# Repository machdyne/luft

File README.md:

# Luft Air Sensor Controller

Luft is an experimental open-source air sensor controller with sockets for up to four MQ gas sensor modules. In addition to MQ modules, you can also connect a SEN55 module (particulate matter, Volatile Organic Compounds, Nitrogen Oxides, humidity, and temperature) and a I2C oxygen sensor, CO₂ sensor, or other I2C sensors.

Luft enables remote monitoring of gasses, air quality and other environmental factors.

The alarm can be triggered by either the MCU or the MQ modules based on their potentiometer setting. The alarm is only activated when JP1 is shunted with a jumper or key switch.

This repo contains schematics, PCB layouts, a DIN-mountable 3D-printable case, and documentation.

Find more information on the [Luft product page](https://machdyne.com/product/luft-air-sensor-controller/).

## Configuration (Tasmota)

### Template

```
{"NAME":"LUFT-ESP32C3","GPIO":[8546,8547,1,8545,8544,1,3872,416,1,1,480,0,0,0,0,0,0,0,1,1,608,640],"FLAG":0,"BASE":1}
```

### Pinout

| GPIO | Function | Description |
| ---- | -------- | ----------- |
| GPIO0 | ADC MQ 3 | MQ3 analog |
| GPIO1 | ADC MQ 4 | MQ4 analog |
| GPIO3 | ADC MQ 2 | MQ2 analog |
| GPIO4 | ADC MQ 1 | MQ1 analog |
| GPIO6 | OUTPUT LOW | MQ power enable |
| GPIO7 | PWM 1 | Fan power control |
| GPIO10 | BUZZER | Buzzer power control |
| GPIO20 | I2C SCL | I2C clock |
| GPIO21 | I2C SDA | I2C data |

### Example Rules

```
# Send MQTT data every 60 seconds
TelePeriod 60

# Socket 1: MQ-135 (GPIO4)
AdcGpio4 135.00, 605.18, -3.937, 15.0

# Socket 2: MQ-2 (GPIO3)
AdcGpio3 2.00, 574.25, -2.22, 15.0

# Socket 3: MQ-6 (GPIO0)
AdcGpio0 6.00, 574.25, -2.22, 15.0

# Socket 4: MQ-9 (GPIO1)
AdcGpio1 9.00, 574.25, -2.22, 15.0
```

### Notes

If you have issues detecting the SEN55 module: https://github.com/arendst/Tasmota/discussions/19027

## Safety

This is an experimental design, use at your own risk. The heating elements in MQ modules can potentially ignite gasses. Luft is intended to be used with the 3D-printable case and an exhaust fan.

## License

The contents of this repo are released under the [Lone Dynamics Open License](LICENSE.md).

Note: You can use these designs for commercial purposes but we ask that instead of producing exact clones, that you either replace our trademarks and logos with your own or add your own next to ours.

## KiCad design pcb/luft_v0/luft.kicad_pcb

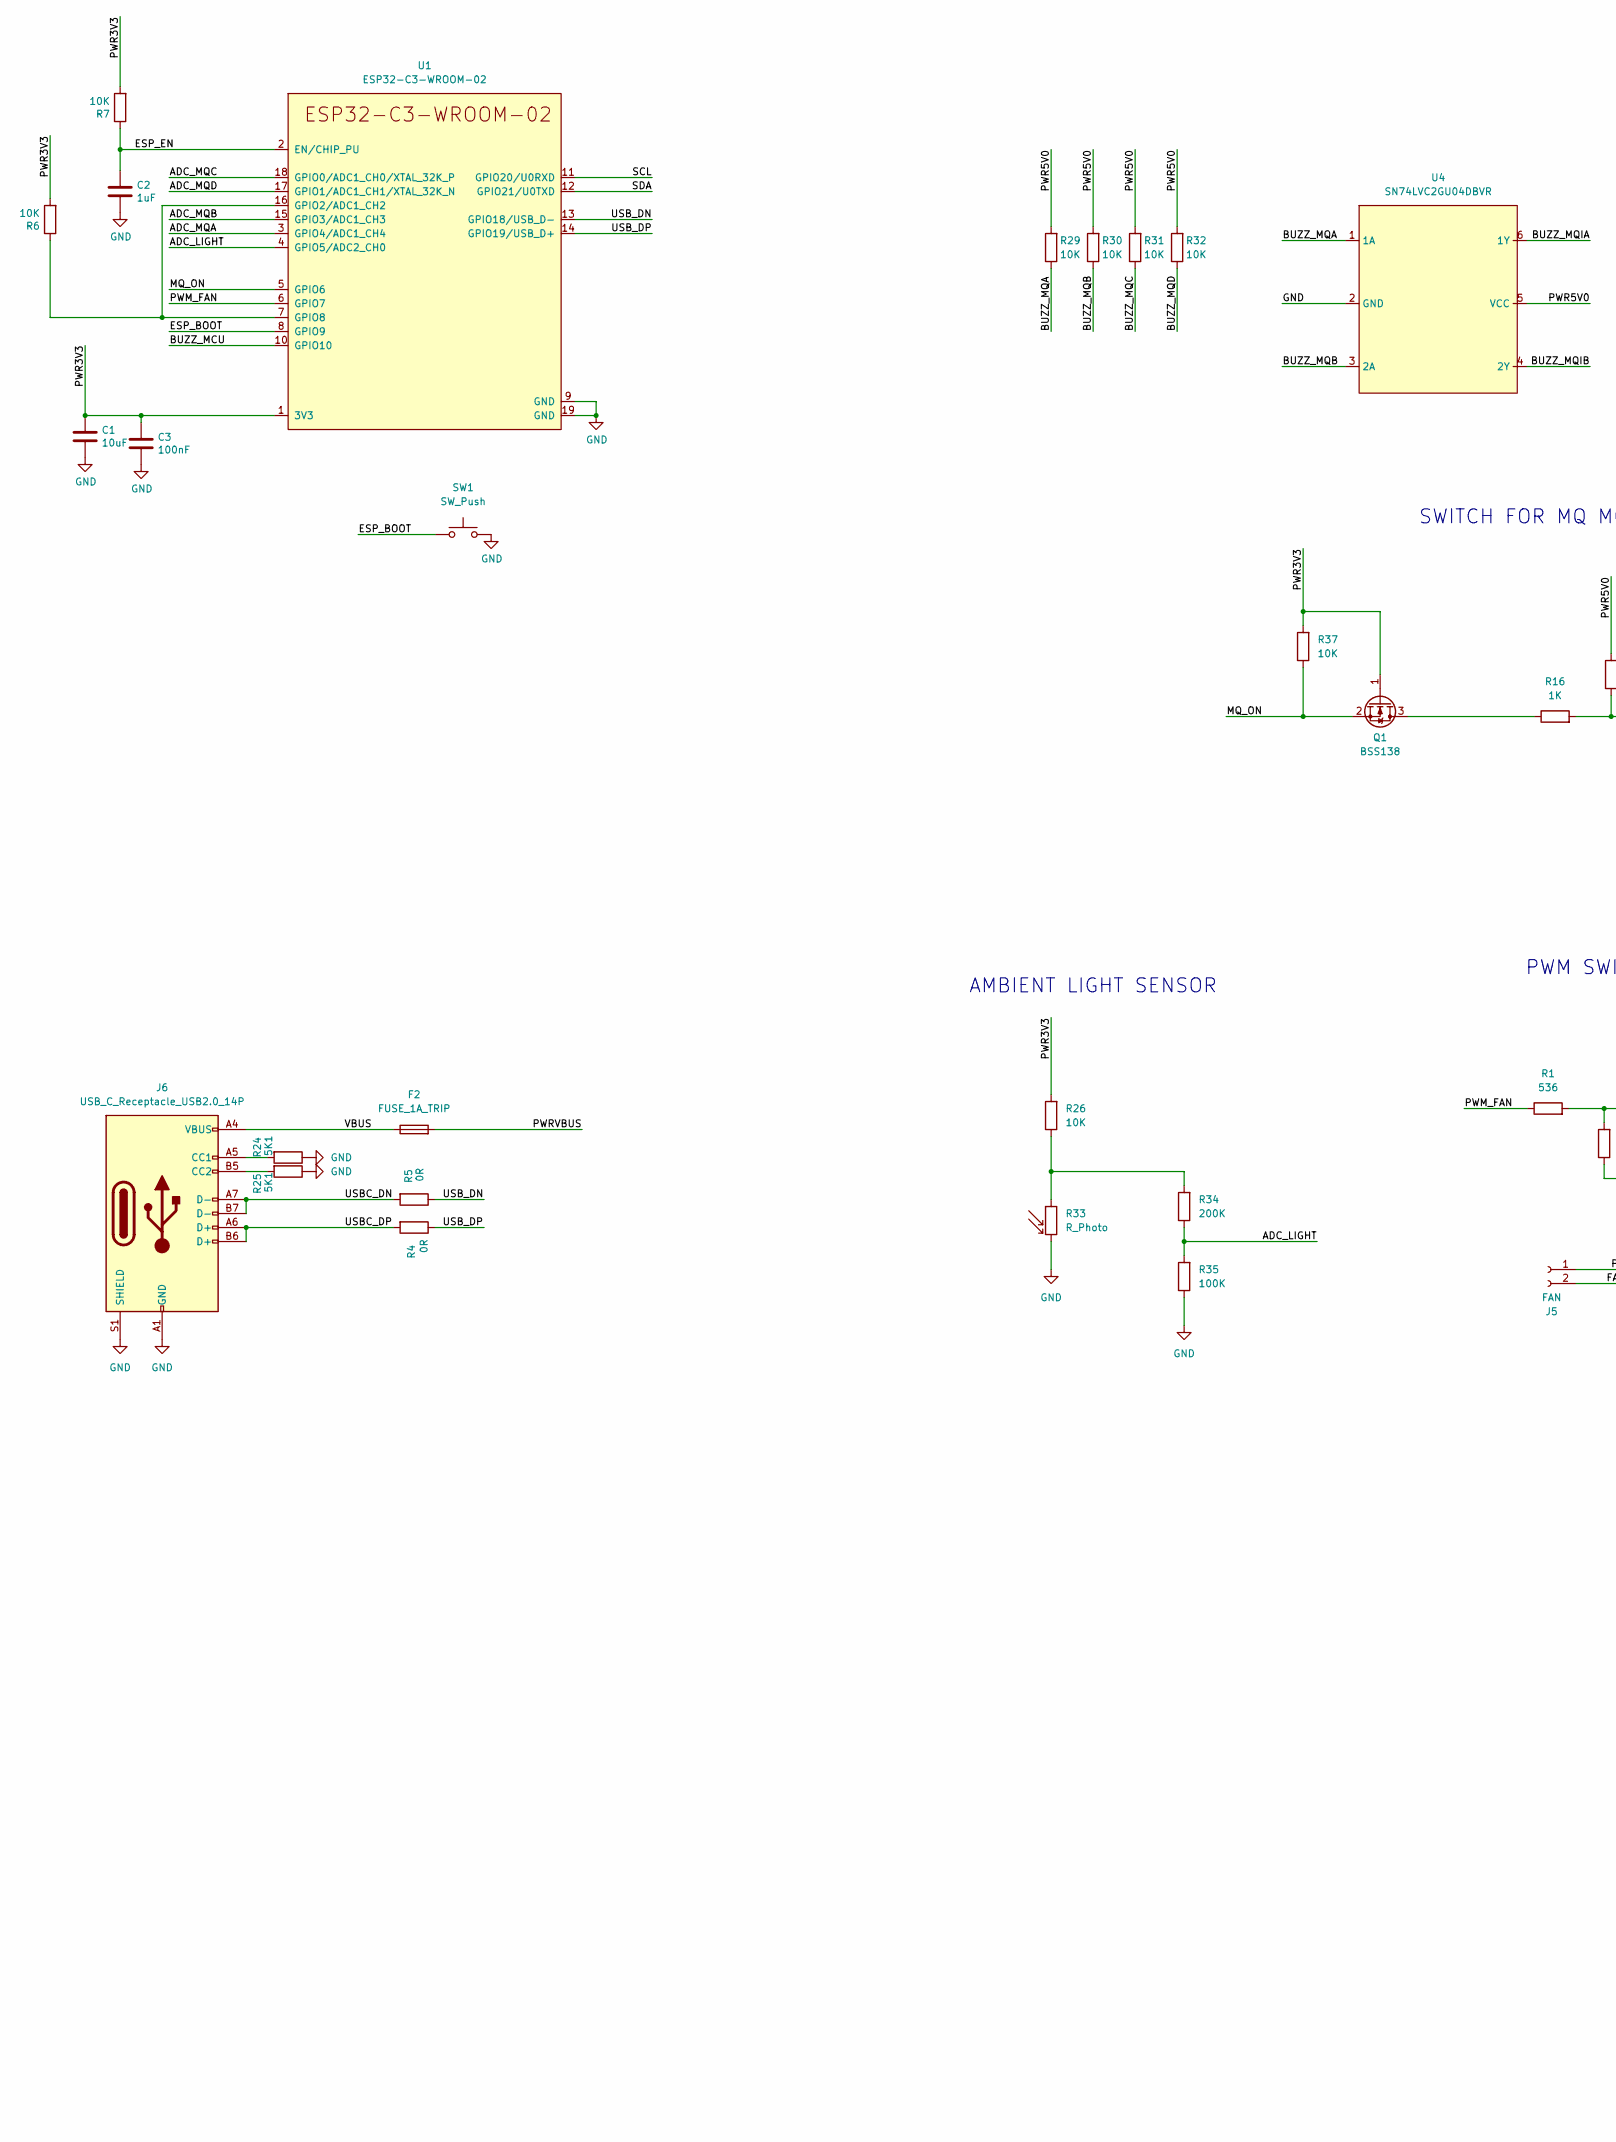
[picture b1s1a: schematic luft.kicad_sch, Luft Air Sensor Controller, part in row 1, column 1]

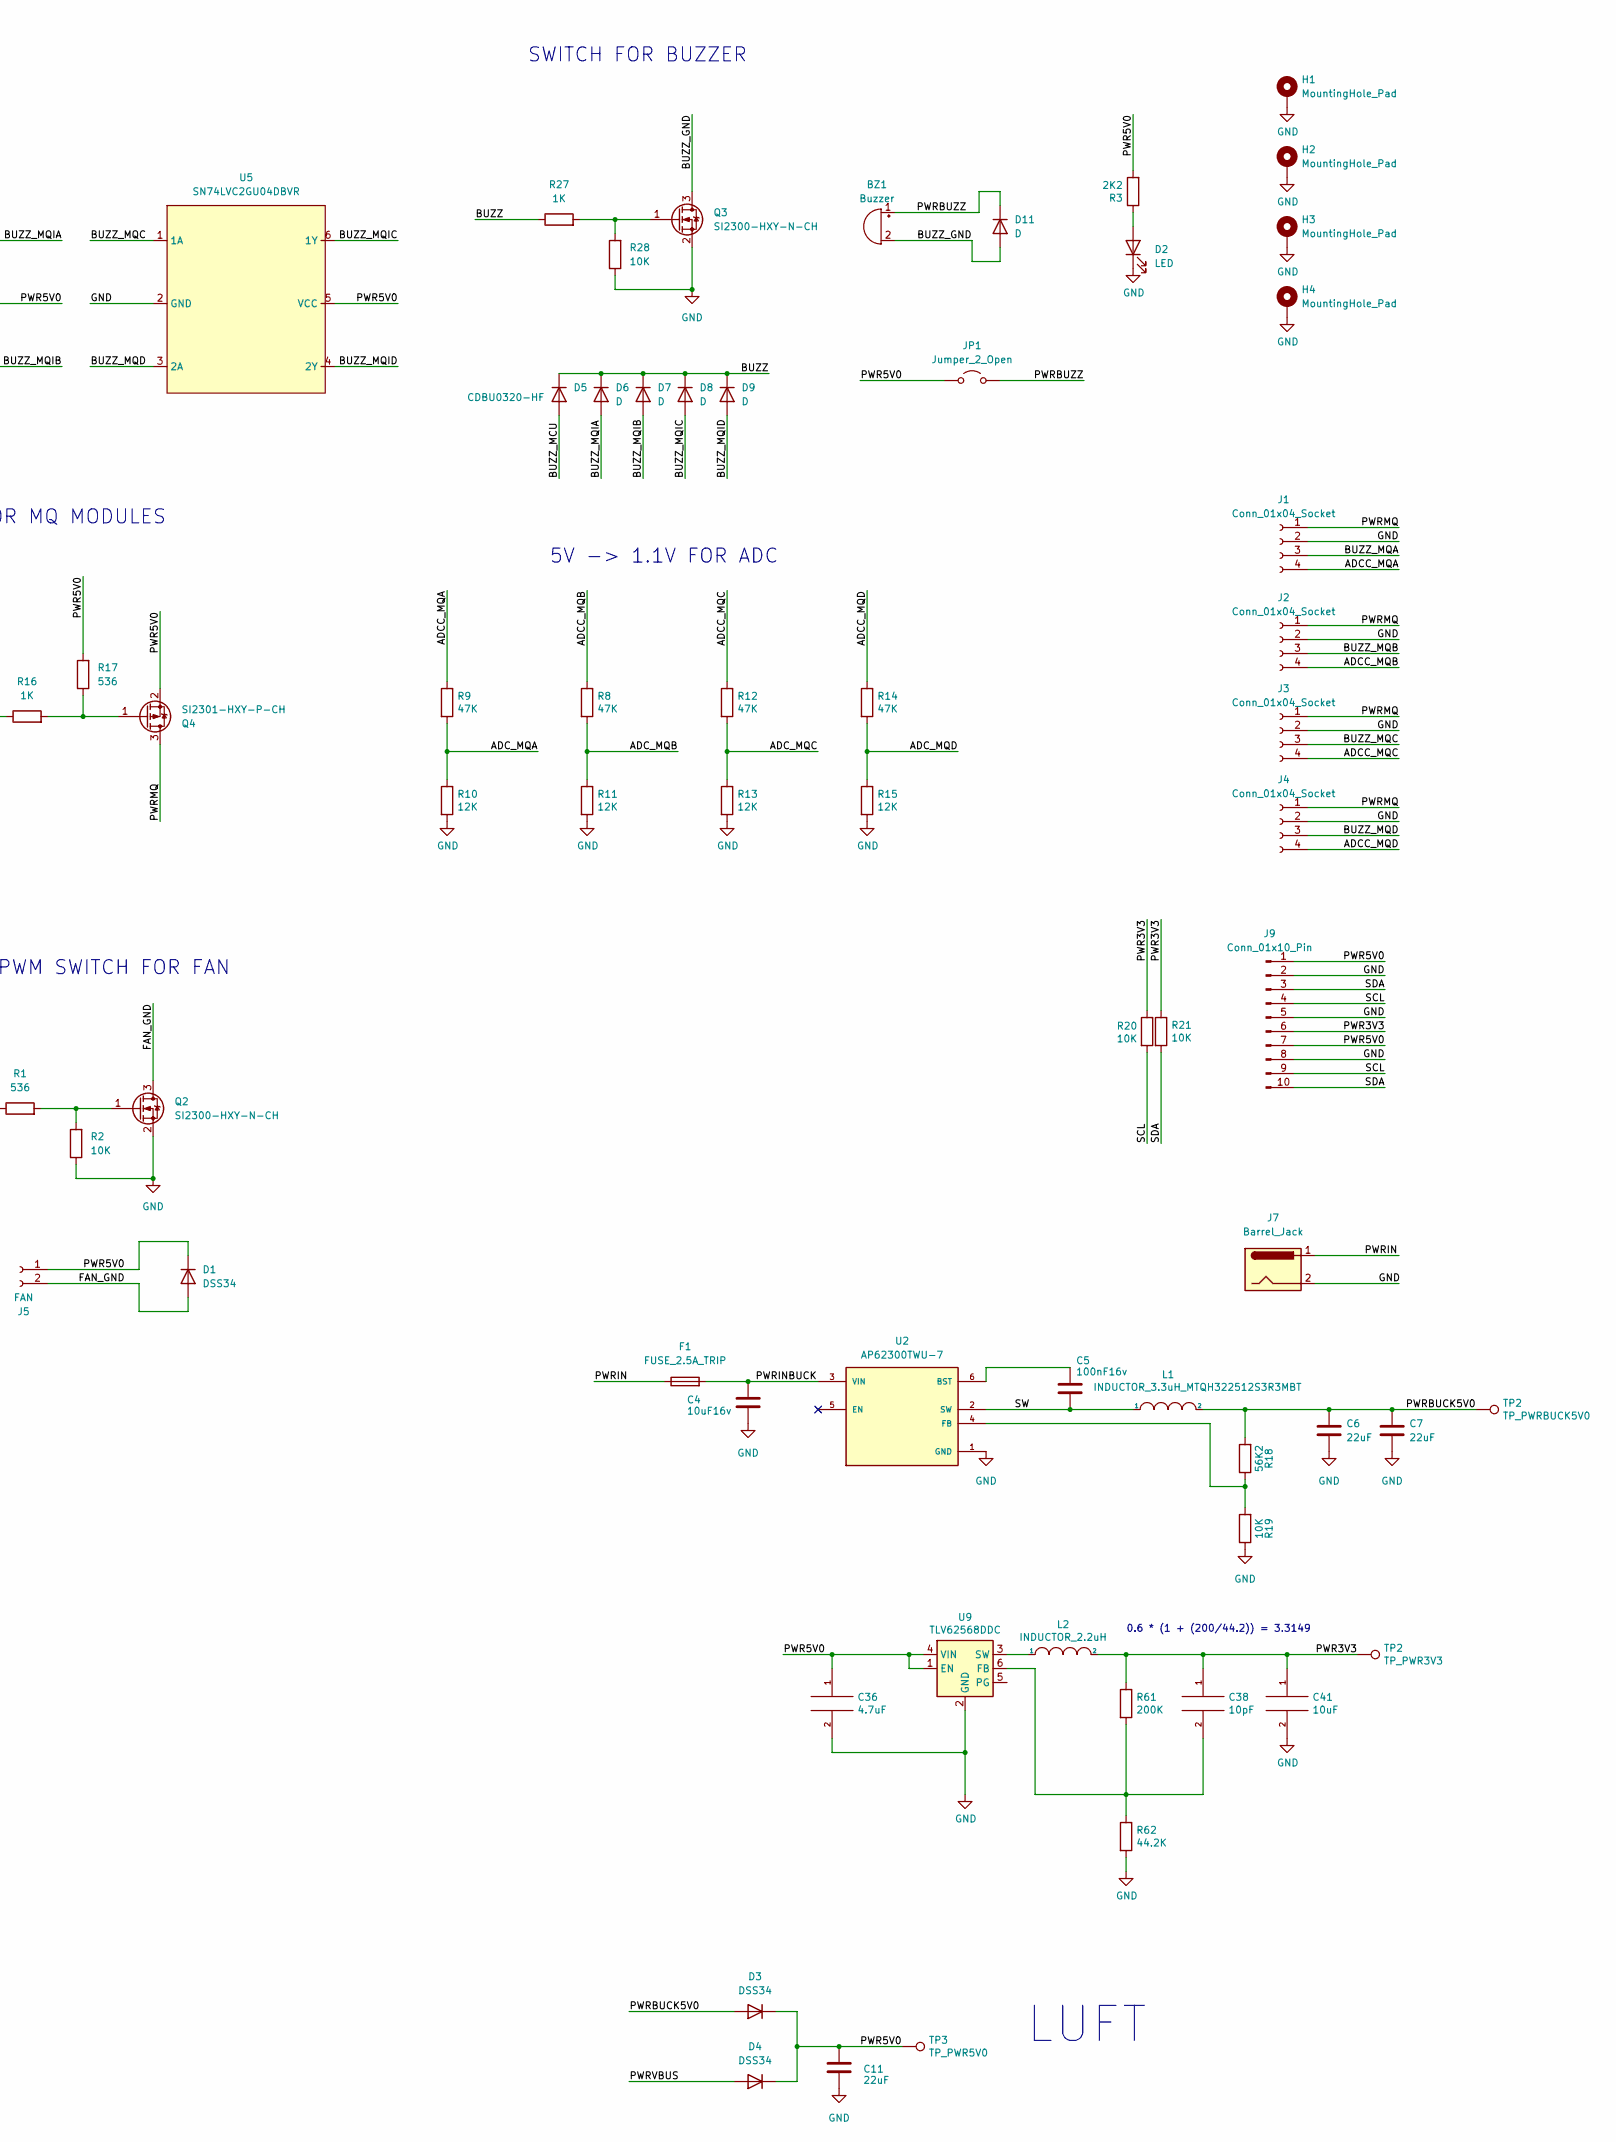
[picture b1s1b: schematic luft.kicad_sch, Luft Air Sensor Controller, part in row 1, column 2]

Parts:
BZ1: Buzzer; Buzzer_12x9.5RM7.6
C1, C41: 10uF; C_0603_1608Metric
C2: 1uF; C_0603_1608Metric
C3: 100nF; C_0603_1608Metric
C4: 10uF16v; C_1206_3216Metric
C5: 100nF16v; C_1206_3216Metric
C6, C7, C11: 22uF; C_0603_1608Metric
C36: 4.7uF; C_0603_1608Metric
C38: 10pF; C_0603_1608Metric
D1, D3, D4: DSS34; D_SMA
D2: LED; LED_1206_3216Metric
D5: CDBU0320-HF; D_0603_1608Metric
D6, D7, D8, D9, D11: D; D_0603_1608Metric
F1: FUSE_2.5A_TRIP; Fuse_1210_3225Metric
F2: FUSE_1A_TRIP; Fuse_1210_3225Metric
H1, H2, H3, H4: MountingHole_Pad; MountingHole_3.2mm_M3_DIN965_Pad
J1, J2, J3, J4: Conn_01x04_Socket; PinSocket_1x04_P2.54mm_Vertical
J5: FAN; JST_XH_B2B-XH-A_1x02_P2.50mm_Vertical
J6: USB_C_Receptacle_USB2.0_14P; USB_C_Receptacle_HRO_TYPE-C-31-M-12-BIG-PADS-PASTE
J7: Barrel_Jack; BarrelJack_GCT_DCJ200-10-A_Horizontal
J9: Conn_01x10_Pin; PinHeader_1x10_P2.54mm_Vertical
JP1: Jumper_2_Open; PinHeader_1x02_P2.54mm_Vertical
L1: INDUCTOR_3.3uH_MTQH322512S3R3MBT; L_1210_3225Metric
L2: INDUCTOR_2.2uH; L_0805_2012Metric
Q1: BSS138; SOT-23
Q2, Q3: SI2300-HXY-N-CH; SOT-23
Q4: SI2301-HXY-P-CH; SOT-23
R1, R17: 536; R_0603_1608Metric
R2, R6, R7, R20, R21, R26, R28, R29, R30, R31, R32, R37: 10K; R_0603_1608Metric
R3: 2K2; R_0603_1608Metric
R4, R5: 0R; R_0603_1608Metric
R8, R9, R12, R14: 47K; R_0603_1608Metric
R10, R11, R13, R15: 12K; R_0603_1608Metric
R16, R27: 1K; R_0603_1608Metric
R18: 56K2; C_0603_1608Metric
R19: 10K; C_0603_1608Metric
R24, R25: 5K1; R_0603_1608Metric
R33: R_Photo; R_PHOTO_3624
R34, R61: 200K; R_0603_1608Metric
R35: 100K; R_0603_1608Metric
R62: 44.2K; R_0603_1608Metric
SW1: SW_Push; Button_2P_3x4mm
TP2: TP_PWRBUCK5V0; TestPoint_THTPad_D1.0mm_Drill0.5mm
TP3: TP_PWR5V0; TestPoint_THTPad_D1.0mm_Drill0.5mm
U1: ESP32-C3-WROOM-02
U2: AP62300TWU-7; SOT95P280X100-6N; PARTREV Rev. 3 - 2
U4, U5: SN74LVC2GU04DBVR; SOT-23-6_Handsoldering
U9: TLV62568DDC; SOT-23-6

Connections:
/ADCC_MQA: J1.4, R9.1
/ADCC_MQB: J2.4, R8.1
/ADCC_MQC: J3.4, R12.1
/ADCC_MQD: J4.4, R14.1
/ADC_LIGHT: R34.1, R35.2, U1.4 (GPIO5/ADC2_CH0)
/ADC_MQA: R9.2, R10.1, U1.3 (GPIO4/ADC1_CH4)
/ADC_MQB: R8.2, R11.1, U1.15 (GPIO3/ADC1_CH3)
/ADC_MQC: R12.2, R13.1, U1.18 (GPIO0/ADC1_CH0/XTAL_32K_P)
/ADC_MQD: R14.2, R15.1, U1.17 (GPIO1/ADC1_CH1/XTAL_32K_N)
/BUZZ: D5.1 (K), D6.1 (K), D7.1 (K), D8.1 (K), D9.1 (K), R27.1
/BUZZ_GND: BZ1.2 (-), D11.2 (A), Q3.3 (D)
/BUZZ_MCU: D5.2 (A), U1.10 (GPIO10)
/BUZZ_MQA: J1.3, R29.1, U4.1 (1A)
/BUZZ_MQB: J2.3, R30.1, U4.3 (2A)
/BUZZ_MQC: J3.3, R31.1, U5.1 (1A)
/BUZZ_MQD: J4.3, R32.1, U5.3 (2A)
/BUZZ_MQIA: D6.2 (A), U4.6 (1Y)
/BUZZ_MQIB: D7.2 (A), U4.4 (2Y)
/BUZZ_MQIC: D8.2 (A), U5.6 (1Y)
/BUZZ_MQID: D9.2 (A), U5.4 (2Y)
/ESP_BOOT: SW1.1, U1.8 (GPIO9)
/ESP_EN: C2.1, R7.1, U1.2 (EN/CHIP_PU)
/FAN_GND: D1.2 (A), J5.2, Q2.3 (D)
/MQ_ON: Q1.2 (S), R37.1, U1.5 (GPIO6)
/PWM_FAN: R1.1, U1.6 (GPIO7)
/PWR5V0: C11.1, D1.1 (K), D3.1 (K), D4.1 (K), J5.1, J9.1, J9.7, JP1.1 (A), Q4.2 (S), R3.2, R17.2, R29.2, R30.2, R31.2, R32.2, TP3.1, U4.5 (VCC), U5.5 (VCC); also elsewhere on the board
/PWRBUZZ: BZ1.1 (+), D11.1 (K), JP1.2 (B)
/PWRIN: F1.1, J7.1
/PWRINBUCK: C4.1, F1.2, U2.3 (VIN)
/PWRMQ: J1.1, J2.1, J3.1, J4.1, Q4.3 (D)
/PWRVBUS: D4.2 (A), F2.2
/SCL: J9.4, J9.9, R20.2, U1.11 (GPIO20/U0RXD)
/SDA: J9.3, J9.10, R21.2, U1.12 (GPIO21/U0TXD)
/SW: C5.2, L1.1, U2.2 (SW)
/USBC_DN: J6.A7 (D-), J6.B7 (D-), R5.2
/USBC_DP: J6.A6 (D+), J6.B6 (D+), R4.2
/USB_DN: R5.1, U1.13 (GPIO18/USB_D-)
/USB_DP: R4.1, U1.14 (GPIO19/USB_D+)
/VBUS: F2.1, J6.A4 (VBUS), J6.A9 (VBUS), J6.B4 (VBUS), J6.B9 (VBUS)
GND: C1.2, C2.2, C3.2, C4.2, C6.2, C7.2, C11.2, D2.1 (K), H1.1, H2.1, H3.1, H4.1, J1.2, J2.2, J3.2, J4.2, J6.A1 (GND), J6.A12 (GND), J6.B1 (GND), J6.B12 (GND), J6.S1 (SHIELD), J7.2, J9.2, J9.5, J9.8, Q2.2 (S), Q3.2 (S), R2.1, R10.2, R11.2, R13.2, R15.2, R19.1, R24.1, R25.1, R28.1, R33.2, R35.1, SW1.2, U1.9 (GND), U1.19 (GND), U2.1 (GND), U4.2 (GND), U5.2 (GND); also elsewhere on the board
unnamed: D2.2 (A), R3.1
unnamed: J6.A5 (CC1), R24.2
unnamed: J6.B5 (CC2), R25.2
unnamed: Q1.3 (D), R16.1
unnamed: Q2.1 (G), R1.2, R2.2
unnamed: Q3.1 (G), R27.2, R28.2
unnamed: Q4.1 (G), R16.2, R17.1
unnamed: R26.1, R33.1, R34.2
unnamed: R6.1, U1.7 (GPIO8), U1.16 (GPIO2/ADC1_CH2)
unnamed: C5.1, U2.6 (BST)
unnamed: R18.1, R19.2, U2.4 (FB)
unnamed 52: L2.1; also elsewhere on the board

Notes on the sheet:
0.6 * (1 + (200/44.2)) = 3.3149
PWM SWITCH FOR FAN
LUFT
AMBIENT LIGHT SENSOR
SWITCH FOR MQ MODULES
SWITCH FOR BUZZER
5V -> 1.1V FOR ADC

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
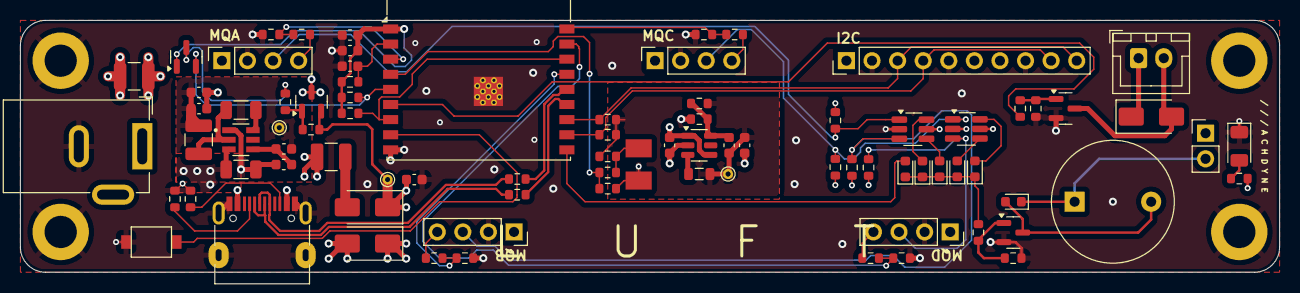
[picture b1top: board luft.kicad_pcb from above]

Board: 4 copper layers, 125.0 x 25.0 mm, 88 parts (0 on the bottom side), 55 nets.

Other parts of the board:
C8: 4.7uF; C_0603_1608Metric
C9: 10pF; C_0603_1608Metric
C10: 10uF; C_0603_1608Metric
R22: 200K; R_0603_1608Metric
R23: 44.2K; R_0603_1608Metric
TP1: TP_PWRBUCK5V0; TestPoint_THTPad_D1.0mm_Drill0.5mm
U3: TLV62568DDC; SOT-23-6

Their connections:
/PWR5V0: C8.1, U3.1 (EN), U3.4 (VIN); also elsewhere on the board
GND: C8.2, C10.2, R23.2, U3.2 (GND); also elsewhere on the board
unnamed: C9.2, R22.2, R23.1, U3.6 (FB)
unnamed 52: U3.3 (SW); also elsewhere on the board

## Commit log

2025-09-18 add render
2025-09-18 improve clips

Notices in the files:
pcb/luft_v0/luft.kicad_sch:
Copyright © 2025 Lone Dynamics Corporation
